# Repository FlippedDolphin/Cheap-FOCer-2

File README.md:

# Cheap FOCer 2 (v1.0)

Low-Cost(around $120 for 5 boards and components) Motor Controller based on the VESC 6

***** caution *******

This is a custom VESC for OpenFFBoard based On Cheap FOCer 2(v1.0)

* Replaced the shunt registers for low current.

* Removed the useless IMU.

* Cleaned up HALL/Encoder lines(for ABN) and COMM lines(for BiSS-C)
  for high frequency signals.(I tested COMM lines only.)

* Added OVP(over voltage protector) for PSU usage.

* Added POWER and MOTOR connector for easy plug.

* Max voltage 50V and max current is 14A.

U8 and J11 are unused, just for test purpose.

I placed JST connector for USB connection(USB1). The normal USB-C connector is J2, but it costs a little more. You can select J2/USB1(If use USB1, you need a converter from USB I/F to JST PH connector. I used cheap USB hub pcb).

A sample BOM and Position are in prodction folder.

bom.org.csv and position.org.csv are come from KiCad.

I used bom.csv and bom.lcsc.csv to order JLCPCB and LCSC respectively.

When I ordered the PCB and parts, I have already had some parts, so my order is minimum.
You need adjust the BOMS for your needs.

I used position.csv for JLCPCB order because original one from Kicad has errors for some parts. You need to check the position when you order yours.

## Warning

* This board has been bench tested with MIGE motor(130st-m10010 and 90ST-M04025) and BiSS-C encoder.
 Hardware or firmware flaws could still exist and affect user operation.
* You are liable for any and all controllers built using this design. This product is intended for hobbyists and not intended for commercial use.
* Do not ask the original auther of Cheap FOCer 2 about this board. He has no responsibility about this board at all.

Licens is followd by the parent project.

## Firmware

The firmware for this board is my bdlc repository with branch "Custom_CFOC2_OpenFFBoard". The Target is "Cheap_FOCer_2_005_nl".

***** caution *******

Front and Back:

Pin outs:

## License

Cheap FOCer 2 is licensed under the Creative Commons Attribution-ShareAlike 4.0 International License. To view a copy of this license, visit <http://creativecommons.org/licenses/by-sa/4.0/.>

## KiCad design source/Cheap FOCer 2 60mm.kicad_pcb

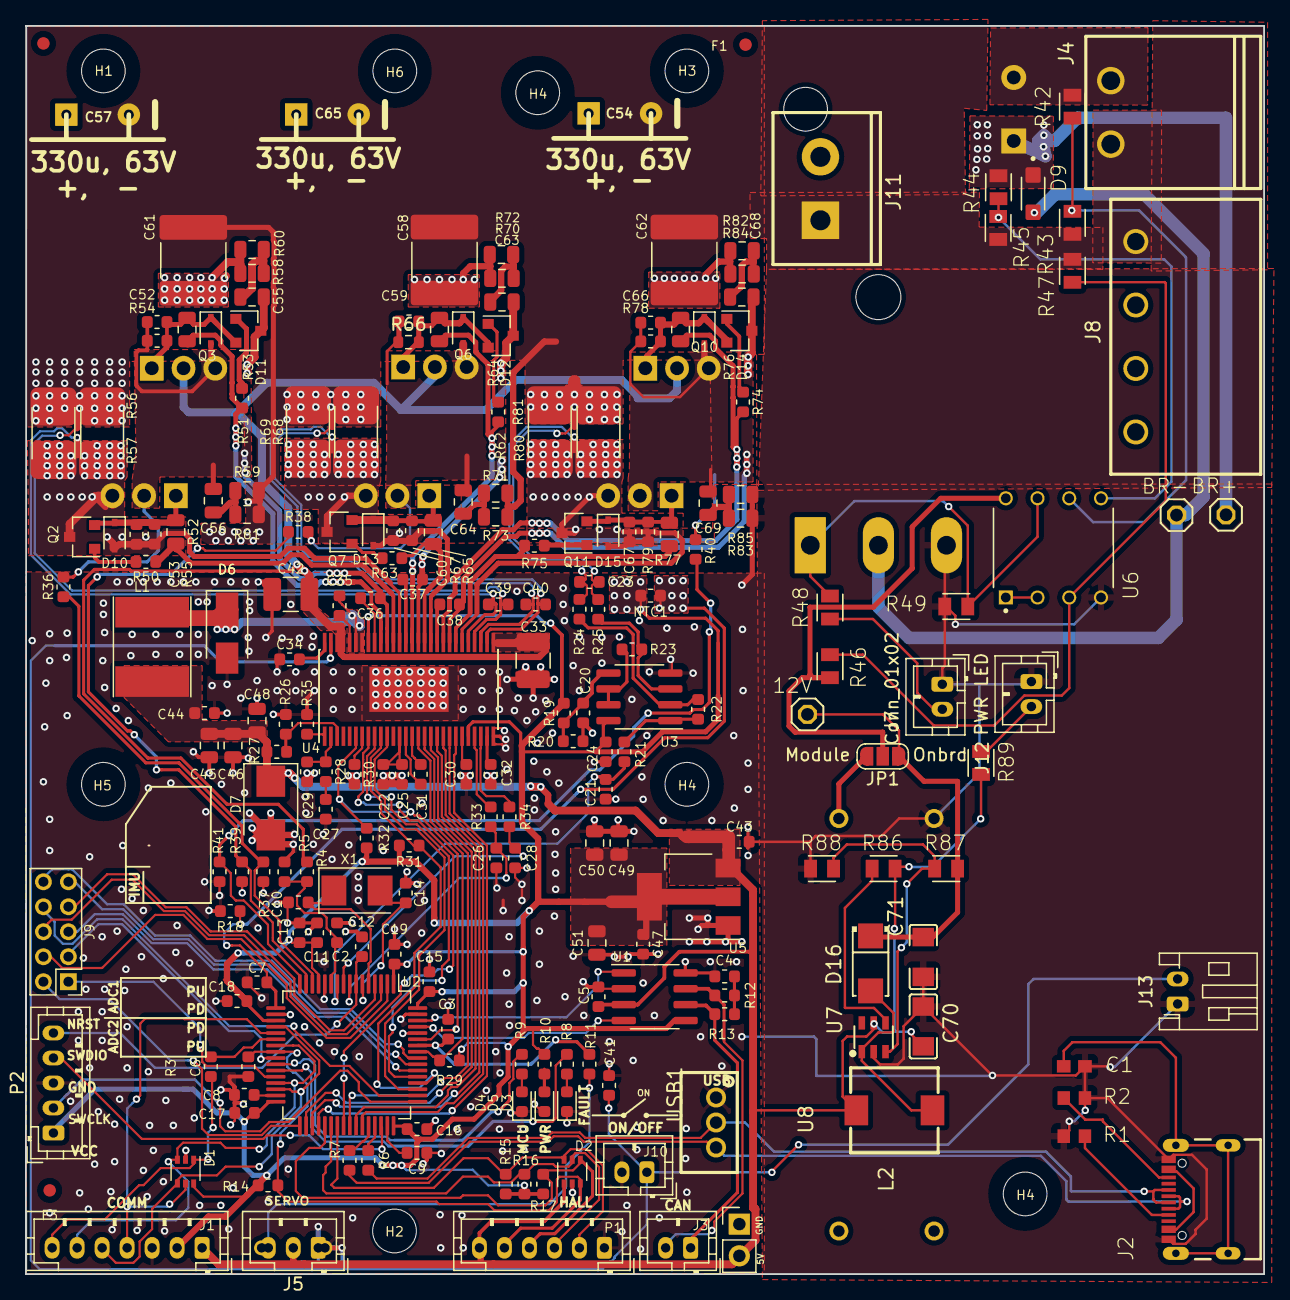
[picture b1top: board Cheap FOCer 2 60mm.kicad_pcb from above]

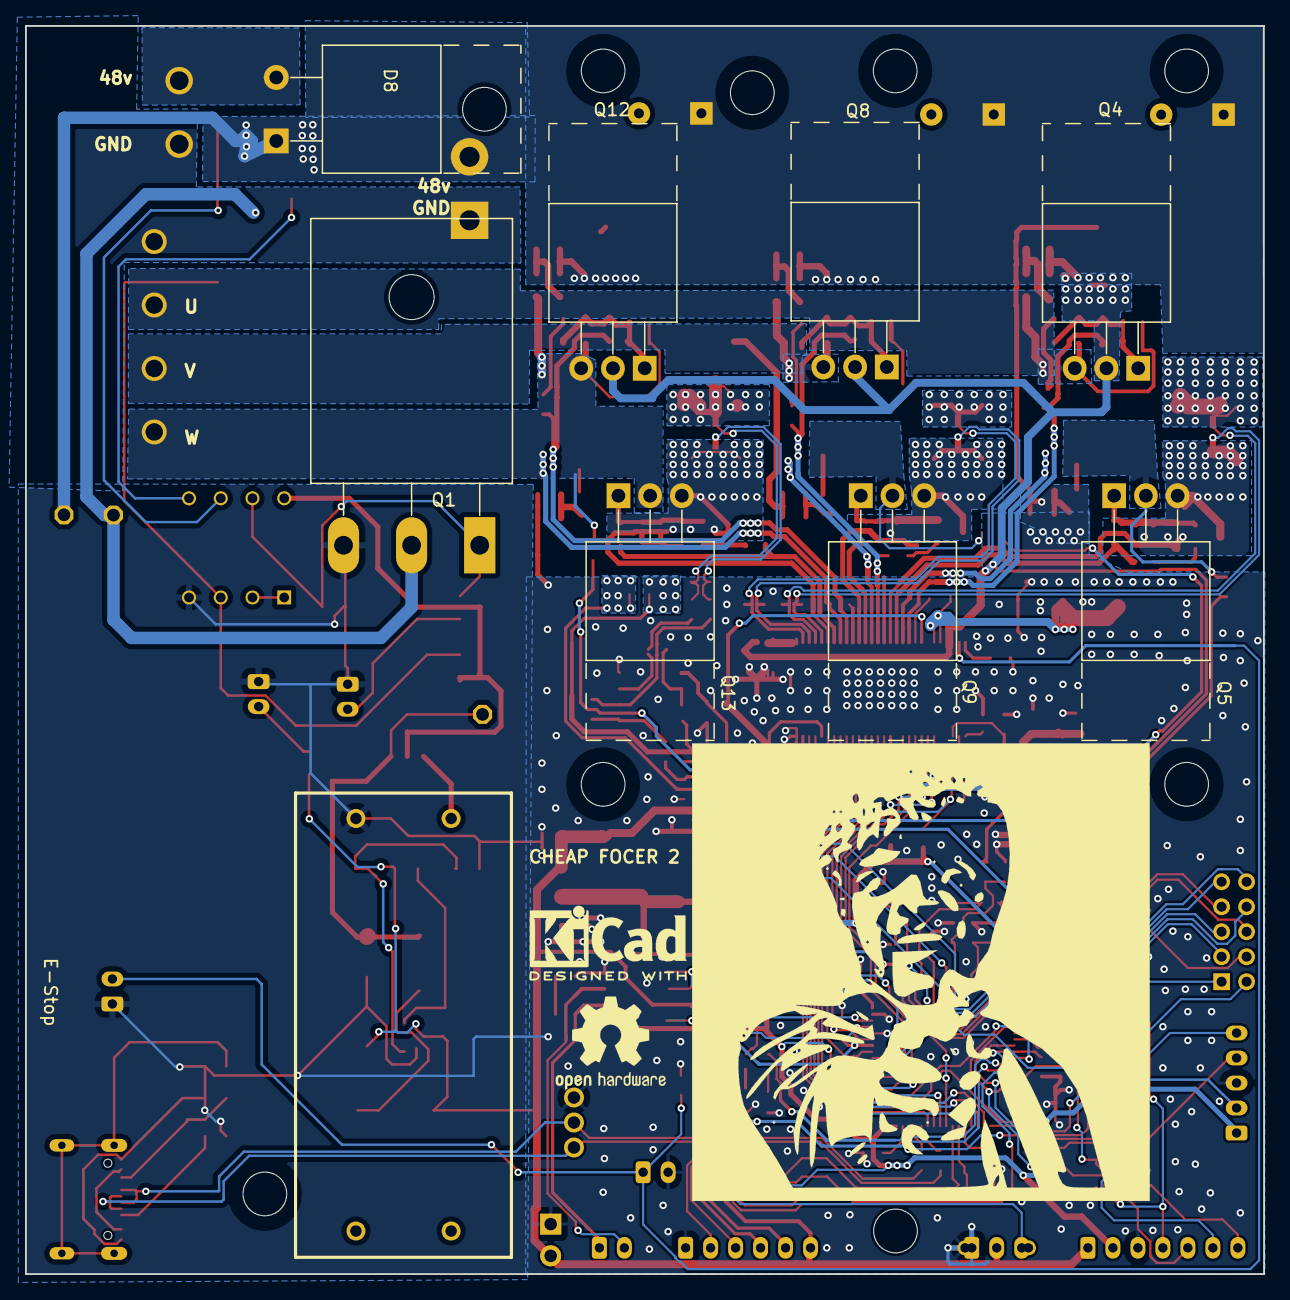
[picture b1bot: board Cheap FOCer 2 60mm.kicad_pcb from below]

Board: 2 copper layers, 99.1 x 99.9 mm, 241 parts (11 on the bottom side), 144 nets.

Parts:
C1: 100nF; C0603
C2, C6, C12, C20, C24, C35, C43: 100n; C_0603_1608Metric
C3: .01uF; C_0603_1608Metric
C4, C21, C23, C26, C28, C39, C40, C66, C67: 1nF; C_0603_1608Metric
C5: 0.1u; C_0603_1608Metric
C7, C8, C9, C11, C13, C15, C16, C17, C18, C19, C47: 2.2u; C_0603_1608Metric
C10, C14: 15p; C_0603_1608Metric
C22, C25, C30, C32, C44: 2.2uF; C_0603_1608Metric
C27: 6.8n; C_0603_1608Metric
C29: 150p; C_0603_1608Metric
C31: 22n; C_0603_1608Metric
C33, C42: 4.7uF, 100V; C_1210_3225Metric_Pad1.42x2.65mm_HandSolder
C34: 15nF; C_0603_1608Metric
C36, C37, C38, C41: 220n; C_0603_1608Metric
C45, C46, C48: 22uf; C_0805_2012Metric
C49, C50, C51: 22uF; C_0805_2012Metric
C52, C53, C59, C60: 2.2nF; C_0603_1608Metric
C54, C57, C65: 330u, 63V; CP_10x20mm_hor_with_model_mirrored_less_silk
C55, C56, C63, C64, C68, C69: 4.7nF, 100V; C_0805_2012Metric
C58, C61, C62: 10uF, 100V; C_2220_5650Metric_Pad1.97x5.40mm_HandSolder
C70, C71: 22uF; C1206
D1, D2: SMF05CT1G; SOT-363_SC-70-6
D3: RED; LED_0603_1608Metric
D4: GRN; LED_0603_1608Metric
D5: BLU; LED_0603_1608Metric
D6: 100v, 1A; D_SMA
D7: D_TVS; D_SMB
D8: STTH3010DTO-220AC_STM; TO-220-2_Horizontal_TabUp
D9: GOODWORK K110; SODFL3618X110N
D10, D11, D12, D13, D14, D15: D_Schottky; D_SOD-323
D16: SS34; SMA_L4.3-W2.6-LS5.2-RD
F1, F2, F3: Fiducial; Fiducial_1mm_Dia_2mm_Outer
H1, H2, H3, H4, H4#2, H4#3, H5, H6: MountingHole; MountingHole_3.2mm_M3_ISO14580_Pad
H7: SLJ; Sam_J
H8: Open Hardware Logo; OSHW-Logo2_9.8x8mm_SilkScreen
H9: KiCAD Logo; KiCad-Logo2_5mm_SilkScreen
J1: Conn_01x07; JST_PH_B7B-PH-K_1x07_P2.00mm_Vertical
J2: USB4105-GF-A; GCT_USB4105-GF-A
J3, J7: Conn_01x02; JST_PH_B2B-PH-K_1x02_P2.00mm_Vertical
J4: Conn_01x02; CONN-TH_2P-P5.08_1757242
J5: Conn_01x03; JST_PH_B3B-PH-K_1x03_P2.00mm_Vertical_hybrid
J6: Conn_01x03; PinHeader_1x02_P2.54mm_Vertical
J8: MotorPower; CONN-TH_MSTBA2.5-4-G-5.08
J9: UNUSED MCU PINS; PinHeader_2x05_P2.00mm_Vertical
J10: On/Off; JST_PH_B2B-PH-K_1x02_P2.00mm_Vertical
J11: VESC_Vin; CONN-TH_1755736
J12: PWR LED; JST_PH_B2B-PH-K_1x02_P2.00mm_Vertical
J13: E-Stop; JST_PH_S2B-PH-K_1x02_P2.00mm_Horizontal
JP1: SolderJumper_3_Open; SolderJumper-3_P1.3mm_Open_RoundedPad1.0x1.5mm_NumberLabels
L1: 22u; L_Taiyo-Yuden_NR-60xx_HandSoldering
L2: 22uH; IND-SMD_L7.0-W6.8
NT1, NT2, NT3, NT4, NT5, NT6: Net-Tie_2; NetTie-2_SMD_Pad0.5mm
NTC1: NTC 10k; R_0603_1608Metric
P1: HALL/Encoder; JST_PH_B6B-PH-K_1x06_P2.00mm_Vertical
P2: Conn_01x05_PH_SWIO; JST_PH_B5B-PH-K_1x05_P2.00mm_Vertical
Q1: FGH40N60SFDTU; TO-247-3_Horizontal_TabUp
Q2, Q3, Q6, Q7, Q10, Q11: Q_PNP_BCE; SOT-23
Q4, Q5, Q8, Q9, Q12, Q13: NCEP60T20; TO-220-3_Horizontal_TabUp_no_hole
R1, R2: 5.1k; R0603
R3: 0R; R_0603_1608Metric
R4, R36, R38, R40: 39k; R_0603_1608Metric
R5, R10, R15, R16, R17, R29, R37, R39, R41: 2k2; R_0603_1608Metric
R6, R7: 22R; R_0603_1608Metric
R8, R9, R11: 100R; R_0603_1608Metric
R12, R13: 60; R_0603_1608Metric
R14, R18, R19, R20, R22, R23, R30, R32: 10k; R_0603_1608Metric
R21, R33, R34: 1.5k; R_0603_1608Metric
R24, R25, R31: 1k; R_0603_1608Metric
R26: 3.3k; R_0603_1608Metric
R27: 18k; R_0603_1608Metric
R28: 15k; R_0603_1608Metric
R35: 220k; R_0603_1608Metric
R42, R44: 20k; RESC2012X65
R43, R45: 1k; RESC2012X65
R46, R47, R49, R86: 10k; RESC2012X65
R48, R89: 560; RESC2012X65
R50, R51, R62, R63, R74, R75: 4.7R; R_0603_1608Metric
R52, R53, R64, R65, R76, R77: 4.7R; R_0805_2012Metric
R54, R55, R66, R67, R78, R79: 4.7k; R_0603_1608Metric
R56, R57, R68, R69, R80, R81: 0.01R; R_2512_Yageo_big_pads
R58, R59, R60, R61, R70, R71, R72, R73, R82, R83, R84, R85: 10R; R_0805_2012Metric
R87: 62K; RESC2012X65
R88: 3k3; RESC2012X65
TP1: 12V; TP1X01
TP2: BR-; TP1X01
TP3: BR+; TP1X01
U1: TJA1051T/3/1J; SOIC-8_3.9x4.9mm_P1.27mm
U2: STM32F405RGT6; LQFP-64_10x10mm_P0.5mm
U3: TP2604-SR; SOIC-8_3.9x4.9mm_P1.27mm
U4: DRV8301; HTSSOP-56-1EP_6.1x14mm_P0.5mm_EP3.61x6.35mm
U5: AMS1117-3.3; SOT-223-3_TabPin2
U6: LM358P; DIP794W45P254L959H508Q8
U7: MT3608; SOT-23-6_L2.9-W1.6-P0.95-LS2.8-BL(MT3608)
U8: MT3608_Modle; MT3068_Module
USB1: Conn_01x03; CONN-TH_B3B-PH-K-S
X1: 8MHz 10ppm (X50328MSB2GI); Crystal_SMD_5032-2Pin_5.0x3.2mm

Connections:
+5V: C5.1, C43.2, C44.2, C45.2, C46.2, C48.2, C70.1, D2.1 (K), D7.1 (A1), J1.1, J5.2, J6.2, L1.2, L2.1, P1.6, R27.1, R86.2, R89.2, U1.3 (VDD), U5.3 (VI), U7.5 (IN)
/12VBoost/VOUT+: C71.1, D16.1 (C), JP1.1 (A), R87.2, TP1.1
/12VBoostModule/VOUT+: JP1.3 (B), U8.3 (Vout+)
/48Vin: D8.2 (A), J4.2 (48v), R42.2
/CAN bus transceiver/CANH: J3.2, R12.1, U1.7 (CANH)
/CAN bus transceiver/CANL: J3.1, R13.2, U1.6 (CANL)
/CAN bus transceiver/CAN_RX: U1.4 (RXD), U2.61 (PB8)
/CAN bus transceiver/CAN_TX: U1.1 (TXD), U2.62 (PB9)
/Filters/HALL1_IN: D2.4 (K), P1.4, R17.1, U2.37 (PC6)
/Filters/HALL2_IN: D2.5 (K), P1.3, R16.1, U2.38 (PC7)
/Filters/TEMP_IN: C6.2, D2.3 (K), P1.5, R14.1, U2.24 (PC4(ADC12_IN14))
/HALL3: D2.6 (K), P1.2, R15.1, U2.39 (PC8)
/MCU/ADC_TEMP: C7.1, NTC1.2, R18.1, U2.17 (PA3(ADC123_IN3))
/MCU/AN_IN: C2.2, R4.2, R5.2, U2.11 (PC3(ADC123_IN13))
/MCU/BR_SO1: C26.2, R33.1, U2.8 (PC0(ADC123_IN10))
/MCU/BR_SO2: C28.2, R34.1, U2.9 (PC1(ADC123_IN11))
/MCU/BR_SO3: C21.2, R21.1, U2.10 (PC2(ADC123_IN12))
/MCU/CS: U2.40 (PC9), U4.8 (nSCS)
/MCU/EN_GATE: R29.1, U2.57 (PB5), U4.16 (EN_GATE)
/MCU/FAULT: R32.2, U2.59 (PB7), U4.6 (FAULT)
/MCU/H1: U2.41 (PA8), U4.17 (INH_A)
/MCU/H2: U2.42 (PA9(OTG_FS_VBUS)), U4.19 (INH_B)
/MCU/H3: U2.43 (PA10), U4.21 (INH_C)
/MCU/L1: U2.34 (PB13(OTG_HS_VBUS)), U4.18 (INL_A)
/MCU/L2: U2.35 (PB14), U4.20 (INL_B)
/MCU/L3: U2.36 (PB15), U4.22 (INL_C)
/MCU/LED_GREEN: R9.2, U2.26 (PB0(ADC12_IN8))
/MCU/LED_RED: R8.2, U2.27 (PB1(ADC12_IN9))
/MCU/MISO_ADC_EXT2: R3.1, U2.22 (PA6(ADC12_IN6))
/MCU/SDI: U2.53 (PC12), U4.9 (SDI)
/MCU/SDO: R31.1, U2.52 (PC11), U4.10 (SDO)
/MCU/SENS1: R36.2, R37.2, U2.14 (PA0(ADC123_IN0/WKUP))
/MCU/SENS2: R38.2, R39.2, U2.15 (PA1(ADC123_IN1))
/MCU/SENS3: R40.2, R41.2, U2.16 (PA2(ADC123_IN2))
/MCU/SERVO: C3.2, R11.1, U2.58 (PB6)
/MCU/SLCK: U2.51 (PC10), U4.11 (SCLK)
/MCU/USB_DM: R7.1, U2.44 (PA11)
/MCU/USB_DP: R6.1, U2.45 (PA12)
/MISO_RX_SCL_IN: D1.1 (K), J1.7, R3.2
/Mosfet driver/GH_A: R51.2, R53.2, U4.47 (GH_A)
/Mosfet driver/GH_B: R62.2, R64.2, U4.42 (GH_B)
/Mosfet driver/GH_C: R74.2, R76.2, U4.37 (GH_C)
/Mosfet driver/GL_A: R50.2, R52.2, U4.45 (GL_A)
/Mosfet driver/GL_B: R63.2, R65.2, U4.40 (GL_B)
/Mosfet driver/GL_C: R75.2, R77.2, U4.35 (GL_C)
/Mosfet driver/H1_LOW: C53.2, D10.2 (A), NT1.2, Q2.3 (C), Q5.3 (S), R55.2, R56.2, R57.2, U4.44 (SL_A)
/Mosfet driver/H1_VS: C36.2, C52.2, C55.1, C56.1, D11.2 (A), J8.2 (W), Q3.3 (C), Q4.3 (S), Q5.2 (D), R36.1, R54.2, U4.46 (SH_A)
/Mosfet driver/H2_LOW: C60.2, D13.2 (A), NT3.2, Q7.3 (C), Q9.3 (S), R67.1, R68.2, R69.2, U4.39 (SL_B)
/Mosfet driver/H2_VS: C37.2, C59.2, C63.1, C64.1, D12.2 (A), J8.3 (V), Q6.3 (C), Q8.3 (S), Q9.2 (D), R38.1, R66.1, U4.41 (SH_B)
/Mosfet driver/H3_LOW: C67.2, D15.2 (A), NT5.2, Q11.3 (C), Q13.3 (S), R79.1, R80.2, R81.2, U4.34 (SL_C)
/Mosfet driver/H3_VS: C38.2, C66.2, C68.1, C69.1, D14.2 (A), J8.4 (U), Q10.3 (C), Q12.3 (S), Q13.2 (D), R40.1, R78.1, U4.36 (SH_C)
/OverVoltageProtector/12V: JP1.2 (C), R46.2, U6.8 (VCC)
/OverVoltageProtector/+IN2: R44.1, R45.2, U6.5 (+IN2)
/OverVoltageProtector/-IN2: R42.1, R43.2, U6.6 (-IN2)
/OverVoltageProtector/BRAKE_RTN: D9.A, Q1.2 (C), TP2.1
/OverVoltageProtector/LED+: J7.2 (LED+), R48.1
/OverVoltageProtector/OUT2: Q1.1 (G), R48.2, R49.2, U6.7 (OUT2)
/RX_SDA_IN: D1.4 (K), J1.5, U2.20 (PA4(ADC12_IN4/DAC1_OUT)), U2.30 (PB11)
/SCK_ADC_EXT_IN: D1.5 (K), J1.4, U2.21 (PA5(ADC12_IN5/DAC2_OUT))
/TX_SCL_MOSI_IN: D1.3 (K), J1.6, U2.23 (PA7(ADC12_IN7)), U2.29 (PB10)
GND: C1.2, C2.1, C3.1, C4.2, C5.2, C6.1, C7.2, C8.2, C9.2, C10.2, C11.1, C12.1, C13.1, C14.2, C15.1, C16.1, C17.1, C18.1, C19.1, C20.2, C21.1, C22.2, C24.1, C25.2, C26.1, C27.1, C28.1, C29.1, C30.2, C32.1, C33.1, C34.2, C41.1, C42.1, C43.1, C44.1, C45.1, C46.1, C47.2, C48.1, C49.1, C50.1, C51.1, C54.2, C57.2, C58.1, C61.1, C62.1, C65.2, C70.2, C71.2, D1.2 (A), D2.2 (A), D3.1 (K), D4.1 (K), D5.1 (K), D6.2 (A), D7.2 (A2), J1.3, J2.A1_B12 (GND), J2.B1_A12 (GND), J4.1 (GND), J5.1, J6.1, J7.1 (LED-), J8.1 (GND), J10.2 (B), J11.1 (GND), J12.1 (LED-), J13.1 (GND), NT2.2, NT4.2, NT6.2, P1.1, P2.3 (GND), Q1.3 (E), R1.1, R2.2, R5.1, R18.2, R20.2, R26.2, R30.1, R35.2, R37.1, R39.1, R41.1, R43.1, R45.1, R47.1, R49.1, R56.1, R57.1, R59.1, R61.1, R68.1, R69.1, R71.1, R73.1, R80.1, R81.1, R83.1, R85.1, R88.1, U1.2 (VSS), U1.8 (Rs), U2.12 (VSSA), U2.18 (VSS), U2.60 (BOOT0(VPP)), U2.63 (VSS), U3.4 (V-), U4.28 (AVGND), U4.57 (GND), U5.1 (GND), U6.4 (GND), U7.2 (GND), U8.4 (Vout-), USB1.1 (GND)
NRST: C12.2, P2.5 (NRST), U2.7 (NRST)
unnamed: C1.1, J2.S1 (SHELL_GND), J2.S2 (SHELL_GND), J2.S3 (SHELL_GND), J2.S4 (SHELL_GND)
unnamed: C4.1, R12.2, R13.1
unnamed: C27.2, R28.2
unnamed: C55.2, R58.2, R60.2
unnamed: C56.2, R59.2, R61.2
unnamed: C63.2, R70.2, R72.2
unnamed: C64.2, R71.2, R73.2
unnamed: C68.2, R82.2, R84.2
unnamed: C69.2, R83.2, R85.2
unnamed: D3.2 (A), R8.1
unnamed: D4.2 (A), R9.1
unnamed: D5.2 (A), R10.1
unnamed: C35.2, D6.1 (K), L1.1, U4.50 (PH), U4.51 (PH)
unnamed: C53.1, D10.1 (K), Q2.2 (E), Q5.1 (G), R52.1, R55.1
unnamed: C52.1, D11.1 (K), Q3.2 (E), Q4.1 (G), R53.1, R54.1
unnamed: C59.1, D12.1 (K), Q6.2 (E), Q8.1 (G), R64.1, R66.2
unnamed: C60.1, D13.1 (K), Q7.2 (E), Q9.1 (G), R65.1, R67.2
unnamed: C66.1, D14.1 (K), Q10.2 (E), Q12.1 (G), R76.1, R78.2
unnamed: C67.1, D15.1 (K), Q11.2 (E), Q13.1 (G), R77.1, R79.2
unnamed: D16.2 (A), L2.2, U7.1 (SW)
unnamed: J2.A5 (CC1), R1.2
unnamed: J2.B5 (CC2), R2.1
unnamed: J2.A7 (DN1), J2.B7 (DN2), R7.2, USB1.3 (D-)
unnamed: J2.A6 (DP1), J2.B6 (DP2), R6.2, USB1.2 (D+)
unnamed: J5.3, R11.2
unnamed: C41.2, J10.1 (A), J13.2 (E-STOP), U4.55 (EN_BUCK)
unnamed: J12.2 (LED+), R89.1
unnamed: Q2.1 (B), R50.1
unnamed: Q3.1 (B), R51.1
unnamed: Q6.1 (B), R62.1
unnamed: Q7.1 (B), R63.1
unnamed: Q10.1 (B), R74.1
unnamed: Q11.1 (B), R75.1
unnamed: R21.2, R22.1, U3.1
unnamed: C10.1, U2.5 (PH0-OSC_IN), X1.1
unnamed: C14.1, U2.6 (PH1-OSC_OUT), X1.2
unnamed: C8.1, U2.31 (VCAP1)
unnamed: C9.1, U2.47 (VCAP2)
unnamed: R23.2, R25.1, U3.3 (+)
unnamed: R22.2, R24.1, U3.2 (-)
unnamed: C20.1, R19.2, R20.1, U3.5 (+)
unnamed: R23.1, U3.6 (-), U3.7
unnamed: C32.2, U4.27 (AVDD)
unnamed: C36.1, U4.48 (BST_A)
unnamed: C37.1, U4.43 (BST_B)
unnamed: C35.1, U4.52 (BST_BK)
unnamed: C38.1, U4.38 (BST_C)
unnamed: C29.2, R28.1, U4.2 (COMP)
unnamed: C31.2, U4.14 (CP1)
unnamed: C31.1, U4.15 (CP2)
unnamed: R30.2, U4.7 (DTC)
unnamed: C30.1, U4.23 (DVDD)
unnamed: C22.1, C25.1, U4.13 (GVDD)
unnamed: R35.1, U4.1 (RT_CLK)
unnamed: R33.2, U4.25 (S01)
unnamed: R34.2, U4.26 (S02)
unnamed: C34.1, U4.56 (SS_TR)
unnamed: R26.1, R27.2, U4.3 (VSENSE)
unnamed: R46.1, R47.2, U6.3 (+IN1)
unnamed: U6.1 (OUT1), U6.2 (-IN1)
unnamed: R86.1, U7.4 (EN)
unnamed: R87.1, R88.2, U7.3 (FB)
PA15: J9.8, U2.50 (PA15(JTDI))
PB2: J9.1, U2.28 (PB2-BOOT1)
PB3: J9.9, U2.55 (PB3(JTDO/TRACESWO))
PB4: J9.10, U2.56 (PB4(NJTRST))
PB12: J9.2, U2.33 (PB12)
PC5: J9.3, U2.25 (PC5(ADC12_IN15))
PC13: J9.4, U2.2 (PC13_(RTC_AF1))
PC14: J9.6, U2.3 (PC14-OSC32_IN)
PC15: J9.7, U2.4 (PC15-OSC32_OUT)
PD2: J9.5, U2.54 (PD2)
SNA: C39.2, NT1.1, U4.33 (SN2)
SNB: C40.1, NT3.1, U4.31 (SN2)
SNC: C23.1, NT5.1, R24.2
SPA: C39.1, NT2.1, U4.32 (SP1)
SPB: C40.2, NT4.1, U4.30 (SP2)
SPC: C23.2, NT6.1, R25.2
SWCLK: P2.2 (SWCLK), U2.49 (PA14(JTCK-SWCLK))
SWDIO: P2.4 (SWDIO), U2.46 (PA13(JTMS-SWDIO))
VCC: C11.2, C13.2, C15.2, C16.2, C17.2, C18.2, C19.2, C24.2, C47.1, C49.2, C50.2, C51.2, D1.6 (K), J1.2, NTC1.1, P2.1 (Vcc), R10.2, R14.2, R15.2, R16.2, R17.2, R19.1, R29.2, R31.2, R32.1, U1.5 (Vref), U2.1 (VBAT), U2.13 (VDDA), U2.19 (VDD), U2.32 (VDD), U2.48 (VDD), U2.64 (VDD), U3.8 (V+), U4.24 (REF), U4.49 (VDD_SPI), U5.2 (VO)
V_SUPPLY: C33.2, C42.2, C54.1, C57.1, C58.2, C61.2, C62.2, C65.1, D8.1 (K), D9.C (K), J11.2 (48V), Q4.2 (D), Q8.2 (D), Q12.2 (D), R4.1, R44.2, R58.1, R60.1, R70.1, R72.1, R82.1, R84.1, TP3.1, U4.29 (PVDD1), U4.53 (PVDD2), U4.54 (PVDD2)

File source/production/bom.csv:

Designator,Footprint,Quantity,Value,LCSC Part #
C1,C0603,1,100nF,C14663
"C10, C14",603,2,15p,C1644
"C11, C13, C15, C16, C17, C18, C19, C47, C7, C8, C9",603,11,2.2u,C23630
"C12, C2, C20, C24, C35, C43, C6",603,7,100n,C14663
"C21, C23, C26, C28, C39, C4, C40, C66, C67",603,9,1nF,C1588
"C22, C25, C30, C32, C44",603,5,2.2uF,C23630
C27,603,1,6.8n,C1631
C29,603,1,150p,C1594
C3,603,1,.01uF,C57112
C31,603,1,22n,C21122
"C33, C42",1210,2,"4.7uF, 100V",C385986
C34,603,1,15nF,C1596
"C36, C37, C38, C41",603,4,220n,C21120
"C45, C46, C48, C49, C50, C51",805,6,22uf,C45783
C5,603,1,0.1u,C14663
"C52, C53, C59, C60",603,4,2.2nF,C1604
"C55, C56, C63, C64, C68, C69",805,6,"4.7nF, 100V",C565636
"C58, C61, C62",2220,3,"10uF, 100V",C153035
"C70, C71",C1206,2,22uF,C77091
"D1, D2",SOT-363_SC-70-6,2, SMF05CT1G,C15879
"D10, D11, D12, D13, D14, D15",D_SOD-323,6,D_Schottky,C313457
D16,SMA_L4.3-W2.6-LS5.2-RD,1,SS34,C8678
D3,603,1,RED,C2286
D4,603,1,GRN,C72043
D5,603,1,BLU,C965807
D6,D_SMA,1,"100v, 1A",C224219
D7,D_SMB,1,D_TVS,C78395
D8,TO-220-2_Horizontal_TabUp,1,STTH3010DTO-220AC_STM,C73865
D9,SODFL3618X110N,1,GOODWORK K110,C908663
L1,L_Taiyo-Yuden_NR-60xx_HandSoldering,1,22u,C266430
L2,IND-SMD_L7.0-W6.8,1,22uH,C27442
NTC1,603,1,NTC 10k,C76589
"Q10, Q11, Q2, Q3, Q6, Q7",SOT-23,6,Q_PNP_BCE,C8542
"R1, R2",R0603,2,5.1k,C23186
"R10, R15, R16, R17, R29, R37, R39, R41, R5",603,9,2k2,C4190
"R11, R8, R9",603,3,100R,C22775
"R12, R13",603,2,60,C25196
"R14, R18, R19, R20, R22, R23, R30, R32",603,8,10k,C25804
"R21, R33, R34",603,3,1.5k,C22843
"R24, R25, R31",603,3,1k,C21190
R26,603,1,3.3k,C22978
R27,603,1,18k,C25810
R28,603,1,15k,C22809
R3,603,1,0R,C3017805
R35,603,1,220k,C22961
"R36, R38, R4, R40",603,4,39k,C23153
"R42, R44",RESC2012X65,2,20k,C114233
"R43, R45",RESC2012X65,2,1k,C100046
"R46, R47, R49, R86",RESC2012X65,4,10k,C100047
"R48, R89",RESC2012X65,2,560,C137421
"R50, R51, R62, R63, R74, R75",603,6,4.7R,C23164
"R52, R53, R64, R65, R76, R77",805,6,4.7R,C17675
"R54, R55, R66, R67, R78, R79",603,6,4.7k,C23162
"R56, R57, R68, R69, R80, R81",R_2512_Yageo_big_pads,6,0.01R,C2903468
"R58, R59, R60, R61, R70, R71, R72, R73, R82, R83, R84, R85",805,12,10R,C17415
"R6, R7",603,2,22R,C23345
R87,RESC2012X65,1,62K,C137415
R88,RESC2012X65,1,3k3,C114222
U1,SOIC-8_3.9x4.9mm_P1.27mm,1,TJA1051T/3/1J,C38695
U2,LQFP-64_10x10mm_P0.5mm,1,STM32F405RGT6,C15742
U3,SOIC-8_3.9x4.9mm_P1.27mm,1,TP2604-SR,C126446
U4,HTSSOP-56-1EP_6.1x14mm_P0.5mm_EP3.61x6.35mm,1,DRV8301,C98969
U5,SOT-223-3_TabPin2,1,AMS1117-3.3,C6186
U7,SOT-23-6_L2.9-W1.6-P0.95-LS2.8-BL(MT3608),1,MT3608,C84817
X1,Crystal_SMD_5032-2Pin_5.0x3.2mm,1,8MHz 10ppm (X50328MSB2GI),C115962

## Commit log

2024-04-29 Add Caution message
2024-05-02 Modified for OpenFFBoard.
2024-05-02 Removed Firmware Folder.
2024-05-02 Added Images.
2024-05-17 Error fix.
